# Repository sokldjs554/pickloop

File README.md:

# PickLoop

**상품을 집어 옮기고, 실패를 감지해 복구하거나 보류하는 로봇 시스템.**

PyBrain AI AI Robot Engineer(S/W) 지원 검토용 프로젝트다. MuJoCo CPU 물리 시뮬레이션에서 RGB-D 관측 → 학습한 상품 임베딩 → 3D 상면 추정 → SCARA 계획·구동 → Modbus 흡착 → 운반·해제 → 영상과 별도 정답으로 배치 확인을 실행한다. 기존 ReachBench의 실제 pick/place 구현을 조사한 뒤, 품목 구분·실패 복구·장치 통신·운영 증거를 신규 범위로 구현했다.

[새 실물 사진 식별 · 등록 상품 정답과 미등록 오수락](https://pickloop-robot-ops.ykh13571.chatgpt.site/recognition) · [주문 상품 선택부터 배치·보류까지](https://pickloop-robot-ops.ykh13571.chatgpt.site/orders.html) · [주스 오인식 비교](docs/juice-gate.md) · [최신 물리 모델에서 운반 높이 직접 비교하기](docs/current-height.md)

## 로봇 피킹 작업 장면

첫 흡착 실패 뒤 다시 관측한 두 번째 시도다. 전체 영상에서 실패, 운반, 배치 확인 시점으로 이동할 수 있다. 실물 식료품 인식은 별도 매장 사진으로 평가했다. [전체 작업 영상과 원본 실행](https://pickloop-robot-ops.ykh13571.chatgpt.site/#work-scene) · [정답·오답·보류 사진](https://pickloop-robot-ops.ykh13571.chatgpt.site/evidence#photos)

### 매장 사진에서 상품 이름 확인

공개 매장 자료의 81개 상품을 등록했다. 기존 미등록 사진 2,656장의 공식 상품명과 예측을 확인하거나 Codespaces에서 `pickloop recognize 사진.jpg`로 직접 판별할 수 있다. [상품별 공개 데모](https://pickloop-robot-ops.ykh13571.chatgpt.site/evidence#photos) · [재현과 사진별 결과](docs/grocery-catalogue.md)

브라우저에서 **옆면 사진 판정 예시**를 누르면 손에 든 오렌지 주스의 성분 표시를 대조해 상품명을 판정한다. 같은 화면에서 내 사진을 선택할 수 있다. 등록한 스웨덴산 1 L 주스 3종의 포장을 비교하며, 바코드로 확인한 주문 규격을 별도로 표시한다. [실물 사진 판독](https://pickloop-robot-ops.ykh13571.chatgpt.site/recognition#read-package) · [옆면·앞면 사진의 최신 재시험](docs/experiments/side-print-evidence/)

### 지원자가 직접 수정한 복구 규칙

개발 seed 200에서 경로가 막힌 재시도에만 운반 높이를 0.40 m로 올리도록 수정했다. 경로 차단 작업은 변경 전후 19.690초에 완료했고, 보정 오차 작업은 두 번째 시도에서 완료하면서 26.935초에서 24.405초로 줄었다. 다섯 작업의 전후 기록을 PR에 담았다. 추가 개발 seed 201~209의 45쌍은 Codex가 별도로 재현했다. [본인 PR #1](https://github.com/sokldjs554/pickloop/pull/1) · [seed 200 실행 원문](docs/experiments/retry-height/) · [직무별 검증 화면](https://pickloop-robot-ops.ykh13571.chatgpt.site/evidence.html)

- [운영 데모](https://pickloop-robot-ops.ykh13571.chatgpt.site): 로그인 없이 링크로 접근 가능한 실제 기록 재생. 브라우저에서 새 물리 조건을 계산하는 화면이 아니다.
- [공고 대응표](docs/job-requirements-matrix.md) · [아키텍처](docs/architecture.md) · [기여 기록](docs/contributions.md)
- [4정책 비교 명세](docs/ablation-protocol.md) · PR #1 이전 동결 평가 원본: `runs/ablation-heldout/` (576회 완료, 원본·집계 공개)
- [과거 120회 결과](runs/final/summary.md) · [과거 집계 JSON](runs/final/metrics.json) · [과거 trial CSV](runs/final/trials.csv): 1회 기준/3회 복구 비교이며 복구 판단의 단독 효과를 증명하지 않는다.
- [학습·변환 평가](docs/vision-model.md) · [ROS2 실제 통신](docs/ros2-integration.md) · [모바일 확장](docs/mobile-extension.md)

Codex가 6축 팔의 장애물 우회, 재구성 지도에서 6.372 m 폐루프 주행, 빈 지도에서 두 구간 탐색, 48개 로봇 프로세스의 통로 경합을 검증했다. ROS 2 운반 중 취소 5건과 소프트웨어 PLC 재시험 원문도 공개했다. [직무별 실행 결과](https://pickloop-robot-ops.ykh13571.chatgpt.site/evidence.html#slam-route) · [25개 항목 전체 대조](docs/job-requirements-matrix.md)

## Mac에서도 브라우저로 실습하기

[GitHub Codespaces에서 PickLoop 열기](https://codespaces.new/sokldjs554/pickloop?ref=main)를 선택하세요. 처음 시작하면 Python과 시뮬레이션 패키지를 설치합니다. 준비가 끝나면 브라우저 터미널에서 아래 명령을 실행하세요.

```bash
python lab.py run my-current
```

마지막에 `기록 my-current/summary.json`이 출력되면 PR #1이 반영된 현재 정책으로 다섯 작업을 실행한 것입니다. [직접 실습 안내](docs/practice.md)에는 변경 전 커밋을 별도 경로에 열어 실험을 재현하는 방법이 있습니다. 자신의 가설과 판단은 [기록지](RECORD.md)에 남길 수 있습니다.

## 설치와 첫 실행

검증 환경: Linux x86_64, Python3.12, MuJoCo3.3.7, PyTorch2.7.1 CPU, EGL/Mesa 소프트웨어 렌더링, g++. 실물 로봇이나 GPU는 필요 없다. Linux와 다른 OS의 EGL/소켓/파일 잠금 호환성은 확인하지 않았다.

Ubuntu24.04 계열의 시스템 의존성 예:

```bash
sudo apt-get update
sudo apt-get install -y python3-venv libegl1 libgl1-mesa-dri libopengl0 g++ ffmpeg fonts-dejavu-core
python3 -m venv .venv
.venv/bin/pip install --extra-index-url https://download.pytorch.org/whl/cpu -r requirements-lock.txt
.venv/bin/pip install --no-deps -e .
export MUJOCO_GL=egl
export LIBGL_ALWAYS_SOFTWARE=1
.venv/bin/pytest -q
```

훈련된 소형 체크포인트와 생성된 텍스처는 포함되어 있다. Python 환경 lock은 실제 검증 환경에서 추출했다. `scripts/install.sh`도 같은 설치·검증을 실행한다.

```bash
# 정상 / 일시적 흡착 실패 복구 / 복구 불가 보류
.venv/bin/pickloop run --seed 7 --fault normal --out runs/local
.venv/bin/pickloop run --seed 7 --fault suction_once --out runs/local
.venv/bin/pickloop run --seed 7 --fault suction_permanent --out runs/local

# 실제 새 작업을 계산하는 로컬 운영 화면
.venv/bin/pickloop serve --host 127.0.0.1 --port 8000
# 브라우저: http://127.0.0.1:8000
```

로컬 화면의 실시간 모드에서는 주문 실행과 취소가 실제 API를 호출한다. 같은 job ID·내용의 완료 요청은 기존 결과를 반환한다. 한 셀은 한 작업만 실행한다. 중단된 작업은 자동 재실행하지 않고 HOLD_RECOVERY_REQUIRED로 조회된다.

## 재현 명령

```bash
# 현재 checkout의 정책으로 4정책 × 12조건 × 12 seed 새 평가
.venv/bin/python -m pickloop.experiment --out runs/reproduced-ablation

# 완료된 새 평가만 원본 result.json에서 다시 집계
.venv/bin/python -m pickloop.experiment --out runs/reproduced-ablation --aggregate

# 평가와 동일 조건으로 대표 재생을 기록하고 원평가와 대조
.venv/bin/python scripts/record_ablation.py runs/reproduced-ablation --out runs/reproduced-replay
.venv/bin/python scripts/export_ablation.py runs/reproduced-ablation runs/reproduced-replay --dest work/reproduced-web-data

# 과거 120회 기록 재집계: 새 4정책 실험과 합산하지 않음
.venv/bin/pickloop aggregate runs/final

# 모바일 이동→도킹→실제 피킹→셀 퇴장→다음 이동
.venv/bin/python scripts/run_mobile.py --help

# CNN 합성 데이터 훈련 및 검증; 아래 명령은 모델을 교체할 수 있으므로 별도 checkout 권장
.venv/bin/python scripts/train_vision.py --help

# C++ 실제 Modbus 클라이언트
mkdir -p work
g++ -std=c++17 -O2 -Wall -Wextra -Werror cpp/modbus_client.cpp -o work/modbus_client
.venv/bin/pytest tests/test_device.py -q

# 운영 화면 계약 검사
node tests/ui-contract.mjs
```

ROS2 Jazzy는 `ros2/Dockerfile`의 고정 공식 이미지로 빌드한다. [실행 명령과 DDS evidence](docs/ros2-integration.md)에 정상 Action, 취소, 중복 요청, 카메라·관절·clock 실제 수신 기록이 있다. Python 코어용 루트 Dockerfile도 제공하지만 이 세션에서 빌드 검증한 컨테이너는 ROS2 이미지이며 코어는 호스트의 고정 venv에서 검증했다.

## 결과의 의미

PR #1 이전 정책의 동결 비교는 개발 seed200..209와 분리한 seed3000..3011, 12개 조건, 아래 4정책의 576회다. `runs/ablation-heldout` 576회를 완료했다. 최대 3회 정책의 완료율은 단순 재시도 86/144(59.7%), 재관측만 103/144(71.5%), 재관측·재계획 113/144(78.5%)다. 자세한 조건별 결과와 TCP 응답 기한 영향은 [검증 결과](docs/submission-summary.md)에 공개했다. 소스·모델·조건 해시를 고정하고 모든 원본 결과를 집계한다. [조건·동결·군집 부트스트랩 명세](docs/ablation-protocol.md)를 따른다.

| 정책 | 최대 시도 | 실패 후 목표 | 운반·복귀 높이 |
|---|---:|---|---|
| baseline | 1 | 재시도 없음 | 0.30m |
| naive | 3 | 마지막 유효 목표 재사용 | 0.30m |
| reobserve | 3 | RGB-D 재관측 | 0.30m |
| recovery | 3 | RGB-D 재관측 | 재시도 때 0.40m |

세 재시도 정책은 sim 60초/wall 90초의 같은 상한과 안전 검사를 쓴다. naive도 목표를 얻지 못한 상태라면 관측을 재시도하고, 압력으로 하중을 확인하면 어느 정책이든 재접근 대신 운반을 이어간다. `naive→reobserve`는 목표 갱신, `reobserve→recovery`는 경로 높이 변경을 비교한다. 이 특정 정책들에 한정한 절제 실험이며 모든 단순 재시도보다 우수하다는 주장은 아니다.

과거 `runs/final`의 seed1000..1004·120회는 보존한다. 1회/3회라는 시도 예산과 정책이 함께 달라졌으므로 그 차이를 복구 판단의 인과 효과로 해석하지 않는다. 과거 결과와 새 576회는 조건 생성·소스가 달라 통계를 합치지 않는다. 새 조건 JSON의 장애는 정책·시도와 독립적인 절대 sim 시간표이고, `condition=None`인 과거·기본 CLI 시나리오는 첫 관측/첫 시도 기반 장애다.

작업 완료율, 첫 시도 lift 성공률과 첫 시도 최종 완료율, 복구율, 잘못된 배치, 낙하, 금지 충돌, 보류, 재시도, 시간, 처리량을 구분한다. 실패 시간도 처리량 분모에 포함한다. simulator throughput과 measured CPU wall throughput은 별개이며 실물 현장 생산성·ROI를 주장하지 않는다. 장애 시간표·지표 정의는 [아키텍처](docs/architecture.md)와 [비교 명세](docs/ablation-protocol.md)에 공개했다. 종료 시 신선한 장치 응답으로 빈 상태가 확정된 경우에만 밸브 OFF를 확인하고, 부착·하중 추정·출력 불확실성은 유지/보류한다. [정지·출력 정책](docs/hold-policy.md)은 HELD와 밸브 ON을 같은 의미로 취급하지 않는다.

합성 평가에서는 직접 생성한 두 가지 붉은 줄무늬 상자와 합성 미등록 패턴으로 검증했다. 최종 합성 평가에서 known240/240, 지정 unknown120/120을 구분했지만, 이 수치는 실제 상품·임의의 unknown 전반에 대한 성능이 아니다. 초기 확인한 평가 분할은 개발 자료로 재분류했고, 모델 동결 후 새로운 seed30000대에서 최종 평가했다.

## 코드 읽기 순서

`types.py` → `geometry.py` → `perception.py`/`vision_model.py` → `simulation.py` → `device.py`와 `cpp/modbus_client.cpp` → `engine.py` → `journal.py`/`server.py` → `evaluation.py`. 정책 비교는 `conditions.py` → `experiment.py`와 [절제 실험 명세](docs/ablation-protocol.md)를 이어서 읽고, 관련 회귀 테스트·각 실행의 `events.jsonl`을 대조한다. 자세한 질문·설계 판단은 [면접 가이드](docs/interview-guide.md)에 있다.

## 확인된 범위와 남은 공백

운영 화면은 4정책 설명·동일 조건 비교·주요 지표·조건별 원본·시도별 실패 이력과 ROS2/C++/모바일 증거 링크를 제공한다. UNKNOWN의 진단점수는 등록 품목 간 softmax이며 보정된 확률이 아니다. 최종 평가 수치는 배치 완료와 원본 집계 후에만 제시한다.

실제 물리 시뮬레이션, CPU 모델 훈련·추론·TorchScript, TCP Modbus/C++, ROS2 Action/DDS, 동일 작업 엔진을 호출하는 모바일 운동학 시나리오를 실행했다. 웹 데모는 해당 기록을 재생한다. GitHub Actions에서 코어 검증과 Codespaces 실습을 실행했다. [검증 기록](https://github.com/sokldjs554/pickloop/actions).

실물 주스팩의 인쇄 무늬와 색을 확인해 기존과 동일한 매장 사진에서 등록품 정답을 3/54에서 44/54로 높였다. 다른 포장 727장과 과일·채소 1,704장의 오수락은 각각 0건이었다. 보류한 등록품 10장과 중간 모델의 실패도 함께 공개한다. [사진 한 장 판별·전체 결과](docs/carton-recognition.md) · [기존 실험](docs/real-photo-evaluation.md)

| 주요업무 | 추가 실행 근거 |
|---|---|
| 박스 인식과 로봇 배치 | 모의 RGB-D 상자 32개를 추정하고 8건에서 영상·물리 배치를 검증했다. [결과](docs/bin-perception.md) |
| 손목 카메라 보정 | 공개 USDA 실측 88쌍 중 22쌍을 따로 두고 픽셀 예측 오차를 측정했다. [좌표계와 결과](docs/hand-eye.md) |
| 모바일 SLAM | 시뮬레이션 라이다·바퀴 기록으로 세 경로의 점유 지도를 만들고 재방문 보정 효과를 측정했다. [지도와 오차](docs/lidar-slam.md) |
| 도킹·다중 로봇 | 두 모의 AMR가 충전기를 공유한다. 정상 인계와 네 가지 전기 고장 시 보류를 확인했다. [전류·점유 기록](docs/dock-charging.md) |
| 설비 연동 | 기존 C++ 클라이언트와 독립 S7 소프트웨어 PLC를 TCP로 연결해 13단계를 검증했다. [PLC 프로그램과 패킷 기록](docs/plc-interop.md) |

실물 로봇 배포, 흡착 누설·안전 회로, 현장 주행과 실제 충전기·PLC 시운전은 남아 있다. 모바일 주행과 고정 셀 시뮬레이션은 도킹 확인 후 연결한다. [실물 인수시험 절차](docs/hardware-acceptance.md)

사용자가 확인한 PCB 경험은 PADS·ATmega128의 회로 설계/부품 배치/배선과 도구 검증이다. KiCAD나 실물 측정 경험을 추정하지 않는다. [확인 내용과 지원서 표현](docs/pcb-experience.md)을 참고한다. 지원자가 직접 수정한 복구 규칙과 그 전후 실행은 [PR #1](https://github.com/sokldjs554/pickloop/pull/1)에 기록했고, AI가 수행한 학습·독립 검증은 [기여 기록](docs/contributions.md)에 표시했다.

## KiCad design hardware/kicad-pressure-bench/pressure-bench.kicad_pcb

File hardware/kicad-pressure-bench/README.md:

# KiCad pressure-input bench circuit

This practice project develops the 150 Ω shunt example in the [PickLoop hardware acceptance plan](../../docs/hardware-acceptance.md). It contains a schematic and a routed 40 × 23 mm two-layer PCB design. Fabrication, assembly, measurements, and robot integration are pending.

- [KiCad project](pressure-bench.kicad_pro) opens the [schematic](pressure-bench.kicad_sch) and [PCB layout](pressure-bench.kicad_pcb).
- [Schematic preview](pressure-bench.svg) and [PCB layout preview](pressure-bench-layout.svg) are KiCad plots. In the layout preview, red is front copper and blue is back copper.

## Current-to-voltage conversion

J1 pin 1 takes current from an external isolated, current-limited bench source. J2 pin 1 exposes `V_SENSE` for a floating high-impedance voltmeter. Pin 2 on both connectors is `BENCH_RETURN`. R1 is a 150 Ω ±1%, 0.25 W through-hole resistor across the two nets. The PCB shares the return between J1 and J2. Source isolation is external to the PCB.

`V_SENSE = I × R`, measured relative to `BENCH_RETURN`. R1 dissipates 60 mW at nominal full scale. A 22 mA source limit yields up to about 73 mW with the resistor at +1% tolerance.

| Applied current | Nominal voltage | Range from resistor tolerance alone |
| ---: | ---: | ---: |
| 4 mA | 0.600 V | 0.594–0.606 V |
| 12 mA | 1.800 V | 1.782–1.818 V |
| 20 mA | 3.000 V | 2.970–3.030 V |

## CAD verification

KiCad 9.0.2 reported **0 ERC errors or warnings**, **0 DRC violations**, **0 unconnected pads**, and **0 schematic parity issues**. The board uses 0.50 mm traces and a 0.20 mm minimum clearance rule. The schematic netlist associates all three pin-1 terminals (`J1.1`, `J2.1`, `R1.1`) with `V_SENSE` and all three pin-2 terminals with `BENCH_RETURN`.

Run from this directory with the standard KiCad symbol and footprint libraries installed.

```sh
kicad-cli sch erc --exit-code-violations -o /tmp/pressure-bench-erc.rpt pressure-bench.kicad_sch
kicad-cli pcb drc --schematic-parity --exit-code-violations -o /tmp/pressure-bench-drc.rpt pressure-bench.kicad_pcb
```

## Proposed bench check

1. With power disconnected, confirm J1 and J2 share continuity pin-for-pin and measure approximately 150 Ω across pins 1 and 2. Check both connector polarities and the R1 markings.
2. Set up an isolated current source in source mode with output disabled, a maximum 22 mA current limit, and at most 5 V compliance. Connect its positive lead to J1 pin 1 and return to J1 pin 2. Connect a floating voltmeter with ≥10 MΩ input impedance across J2. Keep field supplies, sensors, and controllers disconnected.
3. Source 4, 12, and 20 mA, then return to 4 mA. Record the applied current and measured voltage at each point. Allow for source, meter, and resistor accuracy when comparing measurements to the table. Disable the source before disconnecting the leads.

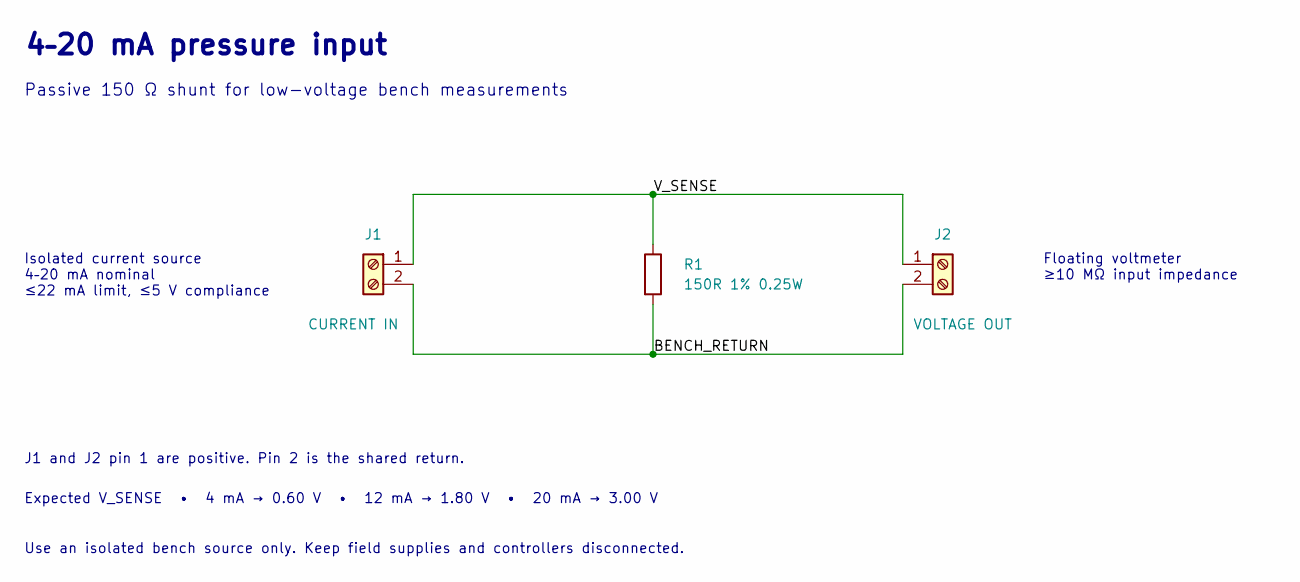
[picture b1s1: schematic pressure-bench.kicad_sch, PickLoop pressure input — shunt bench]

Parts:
J1: CURRENT IN; TerminalBlock_bornier-2_P5.08mm
J2: VOLTAGE OUT; TerminalBlock_bornier-2_P5.08mm
R1: 150R 1% 0.25W; R_Axial_DIN0207_L6.3mm_D2.5mm_P7.62mm_Horizontal

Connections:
/BENCH_RETURN: J1.2, J2.2, R1.2
/V_SENSE: J1.1, J2.1, R1.1

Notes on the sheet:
4–20 mA pressure input
Passive 150 Ω shunt for low-voltage bench measurements
Isolated current source 4–20 mA nominal ≤22 mA limit, ≤5 V compliance
Floating voltmeter ≥10 MΩ input impedance
J1 and J2 pin 1 are positive. Pin 2 is the shared return.
Expected V_SENSE • 4 mA → 0.60 V • 12 mA → 1.80 V • 20 mA → 3.00 V
Use an isolated bench source only. Keep field supplies and controllers disconnected.

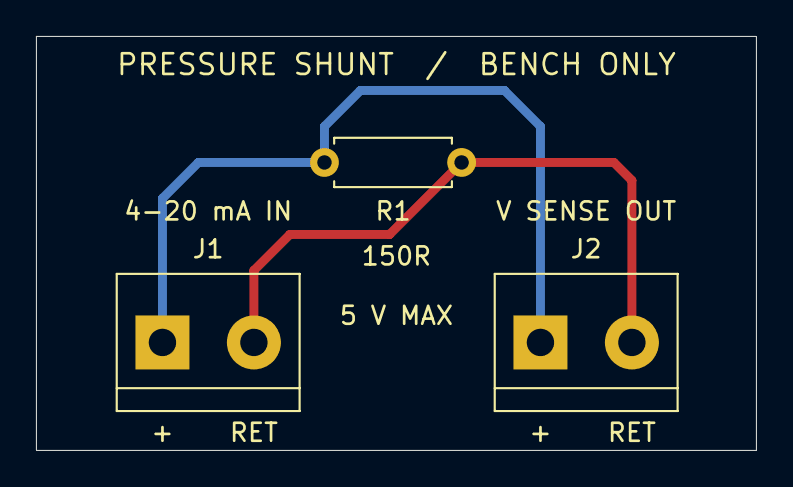
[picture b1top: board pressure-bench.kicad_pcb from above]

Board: 2 copper layers, 40.0 x 23.0 mm, 3 parts (0 on the bottom side), 2 nets.
